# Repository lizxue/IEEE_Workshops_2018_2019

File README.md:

# IEEE_Workshops_2018_2019
18-19 IEEE Workshops Presentations &amp; Files

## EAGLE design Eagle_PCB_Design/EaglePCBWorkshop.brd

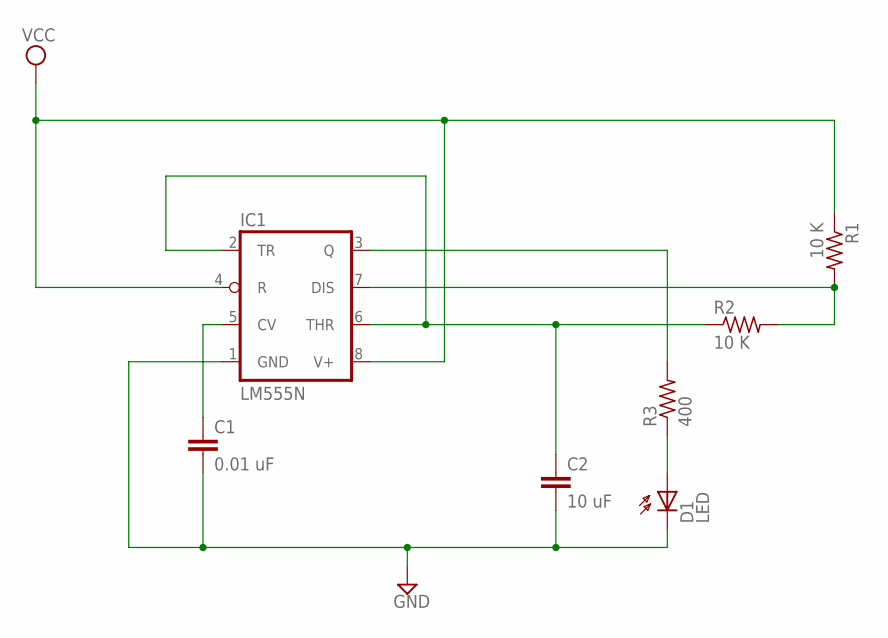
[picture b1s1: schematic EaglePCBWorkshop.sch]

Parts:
C1: 0.01 uF; C5B2.5
C2: 10 uF; C5B2.5
D1: LED; SFH205
IC1: LM555N; DIL08
R1, R2: 10 K; 0204/7
R3: 400; 0204/7

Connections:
GND: C1.2, C2.2, D1.K (C), IC1.1 (GND)
unnamed: C1.1, IC1.5 (CV)
unnamed: C2.1, IC1.2 (TR), IC1.6 (THR), R2.1
unnamed: IC1.7 (DIS), R1.2, R2.2
unnamed: IC1.3 (Q), R3.2
unnamed: D1.A, R3.1
VCC: IC1.4 (R), IC1.8 (V+), R1.1

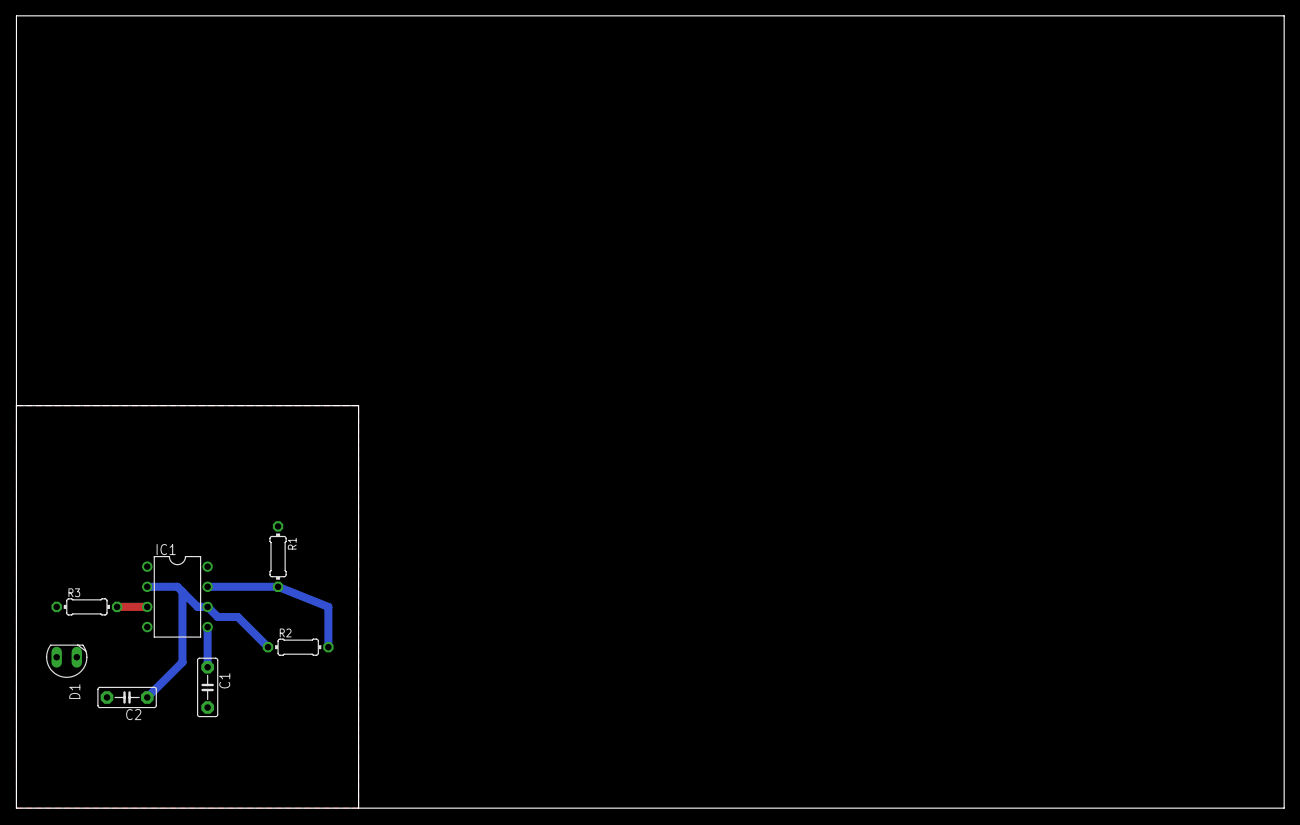
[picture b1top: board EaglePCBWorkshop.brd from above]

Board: 2 copper layers, 160.0 x 100.0 mm, 7 parts (0 on the bottom side), 7 nets.

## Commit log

2019-02-20 Create 7_seg_display_SPIcode
2019-02-20 Create 7_seg_display_I2Ccode
